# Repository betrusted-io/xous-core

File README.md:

# Xous Core

Xous is a microkernel operating system written in pure Rust, built for high-assurance applications.

Key features:
- Hardware memory protection
  - Virtual memory via MMU
  - Each process has an isolated address space
- `std` support in stable Rust (tier-3 Rust target)
- Asynchronous message passing
- Minimal code base
  - [Microkernel](./kernel) architecture
  - System [services](./services) live in userland
- Targeted at high-assurance embedded applications

The [Xous Book](https://betrusted.io/xous-book/) covers the architecture and structure of the kernel.

The [wiki](https://github.com/betrusted-io/betrusted-wiki/wiki) is a community resource that answers many FAQ.

The [Baochip README](./README-baochip.md) is the starting point for Baochip users. `vscode` users may wish to install the `baochip` extension to help manage build & test cycles.

USB CCID (smart-card class) on Baochip is documented in [`docs/ccid/`](./docs/ccid/). It is **not** enabled on default `dabao` / `baosec` images.

The [Precursor README](./README-precursor.md) is the starting point for Precursor users.

> [!IMPORTANT]
> Xous checks version tags as part of the build process. If building from a "shallow clone" or fork, fetch the tags, or else image creation will fail:
```
git remote add upstream https://github.com/betrusted-io/xous-core.git
git fetch upstream --tags
```

## Organization

Xous is a mono-repo project. It contains the kernel, libraries, applications, and tools necessary to build full device images. Here is a brief description of the more important directories:

* **api**: "Secular" API libraries - minimal-dependency, common-core APIs used by core Xous services
* **apps**: Precursor applications
* **apps-dabao**: Dabao applications
* **apps-baosec**: Baosec applications
* **bao1x-boot**: Bao1x secure boot chain
* **baremetal**: Baremetal target - runs after the boot chain, for developers that don't want Xous but can still use Xous' `no-std` features
* **emulation**: Renode scripts used to emulate Xous
* **imports**: Vendored-in libraries that had to be forked for Xous compatibility
* **kernel**: core memory manager, irq manager, and syscall implementations.
* **libs**: Device driver libraries. The common thread is that none of these code bases contain a `main.rs`, just a `lib.rs`.
* **loader**: Sets up virtual memory space and boots the kernel
* **locales**: Tools for handling internationalization
* **signing**: Scripts for generating signed images
* **services**: Xous programs that support Xous apps. Middleware, if you will.
* **svd2utra**: A program for converting SVD chip descriptions in XML to the UTRA "header file" format
* **tools**: Programs used to construct a final boot image. Also the home of various diagnostic and test utilities.
* **utralib**: The [Unambigous Thin Register Abtraction](./utralib/README.md). The core hardware interface for Xous.
* **xous-ipc**: Inter-process communication convenience APIs for Xous
* **xous-rs**: API files for the kernel. Where the syscall interfaces live.
* **xtask**: The build system manager for Xous.

## Dependencies

Install the latest [Rust](https://rust-lang.org/tools/install/) or run `rustup update` to update your Rust installation prior to building. Xous development assumes a recent version of Rust.

## Build Commands

- Precursor: `cargo xtask app-image`
- Dabao: `cargo xtask dabao`
- Dabao with USB CCID: `cargo xtask dabao-ccid`
- Baosec: `cargo xtask baosec`
- Baosec with USB CCID: `cargo xtask baosec-ccid`
- CCID HIL (echo personality, lab only): `cargo xtask ccid-hil`
- Baochip baremetal: `cargo xtask baremetal-bao1x`
- Defcon34: `cargo xtask baosec-lite dc34-console~flash dc34-vault`

Additional apps to be bundled into images can be specified as extra arguments on the command line, e.g. `cargo xtask dabao dabao-console` will generate a Dabao image that includes `dabao-console` in the detached-app section. Features, app-features, loader-features, and so forth can also be passed as command line arguments; run `cargo xtask` on its own for more help.

## Emulation

- `cargo xtask run` will bring up an emulated Precursor
- `cargo xtask baosec-emu` will bring up an emulated Baosec
- `cargo xtask renode-image` will build an image suitable for [Renode](https://renode.io/#downloads) emulation of a Precursor target. Start renode by running `renode emulation/xous-release.resc`

## Building Documentation
A flag of `--feature doc-deps` must be passed when running `cargo doc`, like this:

`cargo doc --no-deps --feature doc-deps`

`doc-deps` is a dummy hardware target that satisfies the requirement of
a "board" when building documentation.

## Local-vs-crates.io Verification

`xtask` does a check every build to ensure that any `crates.io` dependencies
are synchronized with the contents of the monorepo. It protects against the
scenario where you edited a crate that exists in the Xous repo, but the
build system ignores the local edits because it's fetching an old version from
`crates.io`.

Developers working on published crates should patch them in the root `Cargo.toml`
file and bypass the check with `--no-verify`.

## Acknowledgement
This project is funded through the NGI0 PET Fund, a fund established by NLnet
with financial support from the European Commission's Next Generation Internet
programme, under the aegis of DG Communications Networks, Content and Technology
under grant agreement No 825310.

<table>
    <tr>
        <td align="center" width="50%"></td>
        <td align="center"></td>
    </tr>
</table>

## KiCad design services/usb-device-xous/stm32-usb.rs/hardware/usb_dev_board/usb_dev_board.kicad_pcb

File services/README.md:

# Xous Services

Xous is a microkernel OS. The kernel itself is a small program, which runs within just one 4kiB page of RAM. The kernel in and of itself hands out pages from the page table, and routes messages. Everything else is managed by "servers".

Interprocess messages are fast and light-weight in Xous. `Scalar` messages pass data using registers on the stack, and are the fastest messages. `Memory` messages work by remapping memory pages between processes. `send`, `lend`, and `lend_mut` of memory pages is supported. `send` creates a full copy of the page, and is non-blocking; `lend` remaps the page into the borrowing process with read-only privileges, blocking the lending process until the borrowing process returns the page. `lend_mut` is like `lend` but with read/write privileges allowed on the lent memory.

The underlaying hardware is entirely memory-mapped; this includes the notional "disk" which is actually FLASH ROM. Every hardware peripheral has its addresses page-aligned, so that individual peripherals may be "owned" by a given server. The kernel itself "owns" no hardware other than a UART for debugging and a private port into the TRNG.

The kernel starts up a core set of servers, which are broadly divided into three categories:

- "Well known" servers
- "HAL" servers
- "Application" servers

Almost all servers in xous are accessed through a 128-bit, cryptographically random `SID`. These random IDs change with every boot. Thus, in order to connect to a server, one must first resolve its name into an `SID`. In order to facilitate this process, three "well known" servers are provided:

- `xous-names`
- `ticktimer-server`
- `log-server`

These three servers can be accessed by any process, regardless of their trust level, as their `SID` is actually a well-known number. The `ticktimer-server` is well-known so that servers can delay their boot (if necessary; so far it hasn't been). The `log-server` is well-known so that errors in connecting to the name server can be debugged.Please refer to the [README for xous-names](xous-names/README.md) for more details on how name resolution works.

Initially, `xous-names` functions as a permissive oracle that allows kernel servers to freely look up `SID`s using the set of names defined in [names.rs](../xous-rs/src/names.rs). Once the kernel is initialized, a `lockdown` message is sent to `xous-names` which prevents any further lookups on servers that are meant to be private to the kernel. (*TODO*: a coherent, maintainable method for declaring private servers to `xous-names`)

The distinction between "HAL" servers and "Application" servers is fuzzy; but as a rule of thumb, "HAL" servers are private to the kernel and strive for minimal complexity and maximal clarity in their writing. "Application" servers remain discoverable by user applications after the `lockdown` event, and are responsible for gate-keeping and vetting requests to the HAL layer.

An example of this is the `graphics-server` and the `gam`.

The `graphics-server` is a HAL; any process that can talk to it is capable of drawing pixels on the screen at any location. The `graphics-server` implements drawing primitives like `Rectangle`, `Line`, `Circle`, and `TextView`, as message-passing at the pixel level would not be performant. User processes should not be allowed to talk to it, because it would allow user processes to create a fake UI and thus could fool users into typing passwords into fake dialog boxes.

The `gam` is a Graphical Abstraction Manager. It manages various `Canvas` objects that have trust levels associated with them. Primitives such as `TextView` are bound to `Canvas` objects, and the `gam` will handle vetting if the objects are allowed to be drawn, clipping, and so forth. Note that the Xous philosophy is that applications do _not_ get to control the exact look-and-feel of their UI; this is to prevent less trusted applications from masquerading as trusted applications, but also assists with things like accessibility and internationalization. For example, applications cannot pick their font; they can only request a style class such as "small", "regular", and "bold". Thus application developers should think of rendering their UI more as hints and directives to the `gam`, and less as direct pixel pushing.

Conceptually, a complete Xous OS implementation would have HALs that claim the pages of every hardware device, and application servers that claim all the other remaining memory pages -- this includes unused pages and aliased regions -- except for the free memory reserved for applications themselves. Thus, Xous as a kernel does nothing to prevent anyone on its own right from mapping a page; it's up to the complete set of services frameworks to ensure that all the requisite pages have been mapped. (*TODO*: an audit tool to check the memory space and verify that 1. all CSRs and memory spaces explicitly declared in soc.svd are mapped, and 2. checks that otherwise remaining free space is mapped to a "gutter" that panics if accessed).

We're trying to track progress on implementing the various servers using [github projects](https://github.com/betrusted-io/xous-core/projects/1).

## Server Limit

Xous is currently limited to 128 servers. Each potential server reserves 40 bytes of space in the kernel. Xous 0.8 carries about 30 servers, so 128 servers should be reasonably future-proof. Adjusting the limit requires making a change in two places (note the permalink is to an older version of Xous):

1. https://github.com/betrusted-io/xous-core/blob/68aff967e85847cce98e6ec65384f59c803f18a8/kernel/src/services.rs#L19
1. https://github.com/betrusted-io/xous-core/blob/68aff967e85847cce98e6ec65384f59c803f18a8/kernel/src/services.rs#L235

Process count is adjusted by altering https://github.com/betrusted-io/xous-core/blob/master/kernel/src/arch/riscv/process.rs#L15. Xous 0.8 carries about 10 processes, and the current limit is 63. Each additional process reserves about 16 or so additional bytes for tracking information.

## Well-Known Servers
Here is the list of well-known services:
- `ticktimer-server` -- allows processes to know elapsed time since start, and request sleeps. Also manages WDT.
- `xous-names` -- resolves names into `SID`s.
- `log-server` -- implements info and error logging. Has a separate UART from the kernel UART.

## Hal Servers
Here are a list of HALs, implemented and projected, and their functions:

- `com` -- manages requests to and from the EC
- `graphics-server` -- manages the frame buffer and basic drawing primitives. Talks to the MEMLCD
- `keyboard` -- key matrix management; debounce; ScanCode conversion. Keyboard layouts (qwerty, dvorak, azerty, qwertz, braille) are interpreted in this server
- `trng` -- manages the TRNG hardware, provides TRNGs for other processes
- `llio` -- manages I2C, RTC, GPIO, pin interrupts, soft reboot, and power pins. Also home for info, build IDs, etc.
- `codec` -- basic buffering of frames into and out of the audio CODEC
- `jtag` -- manages the JTAG interface (used for key fusing)
- `keys` -- management of cryptographic key store
- `engine25519` -- Engine25519 interface
- `sha512` -- SHA512 interface
- `spinor` -- manages the erasure and programming of the SPINOR
- `ram` -- manages allocation of RAM for applications
- `scheduler` -- manages thread scheduling and priorities

## Application Servers
Here are a list of application servers, implemented and projected, and their functions:
- `fcc-agent` -- use-once -- a special agent meant to run on a minimal Xous for FCC testing. Should never be compiled into production firmware.
- `trng-tester` -- use-once -- a special server used to facilitate testing of the TRNG. Pipes TRNG output to memory regions that can be read out using `bt-rngd` and fed into Dieharder for analysis.
- `gam` -- pre-alpha -- manages `Canvas` objects, and provides an abstract framework for applications. Also manages status bar, context menus and pop-up notifications.
- `ime` -- liases with `keyboard` and `gam` to handle keyboard input
- `pddb` -- plausibly deniable database. Used in lieu of a conventional filesystem for storing key/value pairs in a plausibly deniable fashion.
- `update-ec` -- manages the updating of the EC
- `update-soc` -- manages remote (non-USB) updates of the FPGA and kernel
- `net` -- manages connections to the Internet
- `wifi` -- manages wifi configuration
- `power` -- intermediates requests to the backlight, battery status, charging, RTC, etc.
- `accel` -- intermediates requests to the accelerometer
- `audio` -- intermediates requests to the audio hardware. Does stream mixing, etc.
- `usb` -- handles USB connections
- `credentials` -- trusted PIN/password entry mechanism, manages currently activated credentials

## Applications
Here are a list of user applications:
- `shell` -- refactoring -- provides a "chat-like" interface for talking to Xous
- `chat` -- text and audio secure chat app
- `launcher` -- an application launcher
- `password` -- a password vault

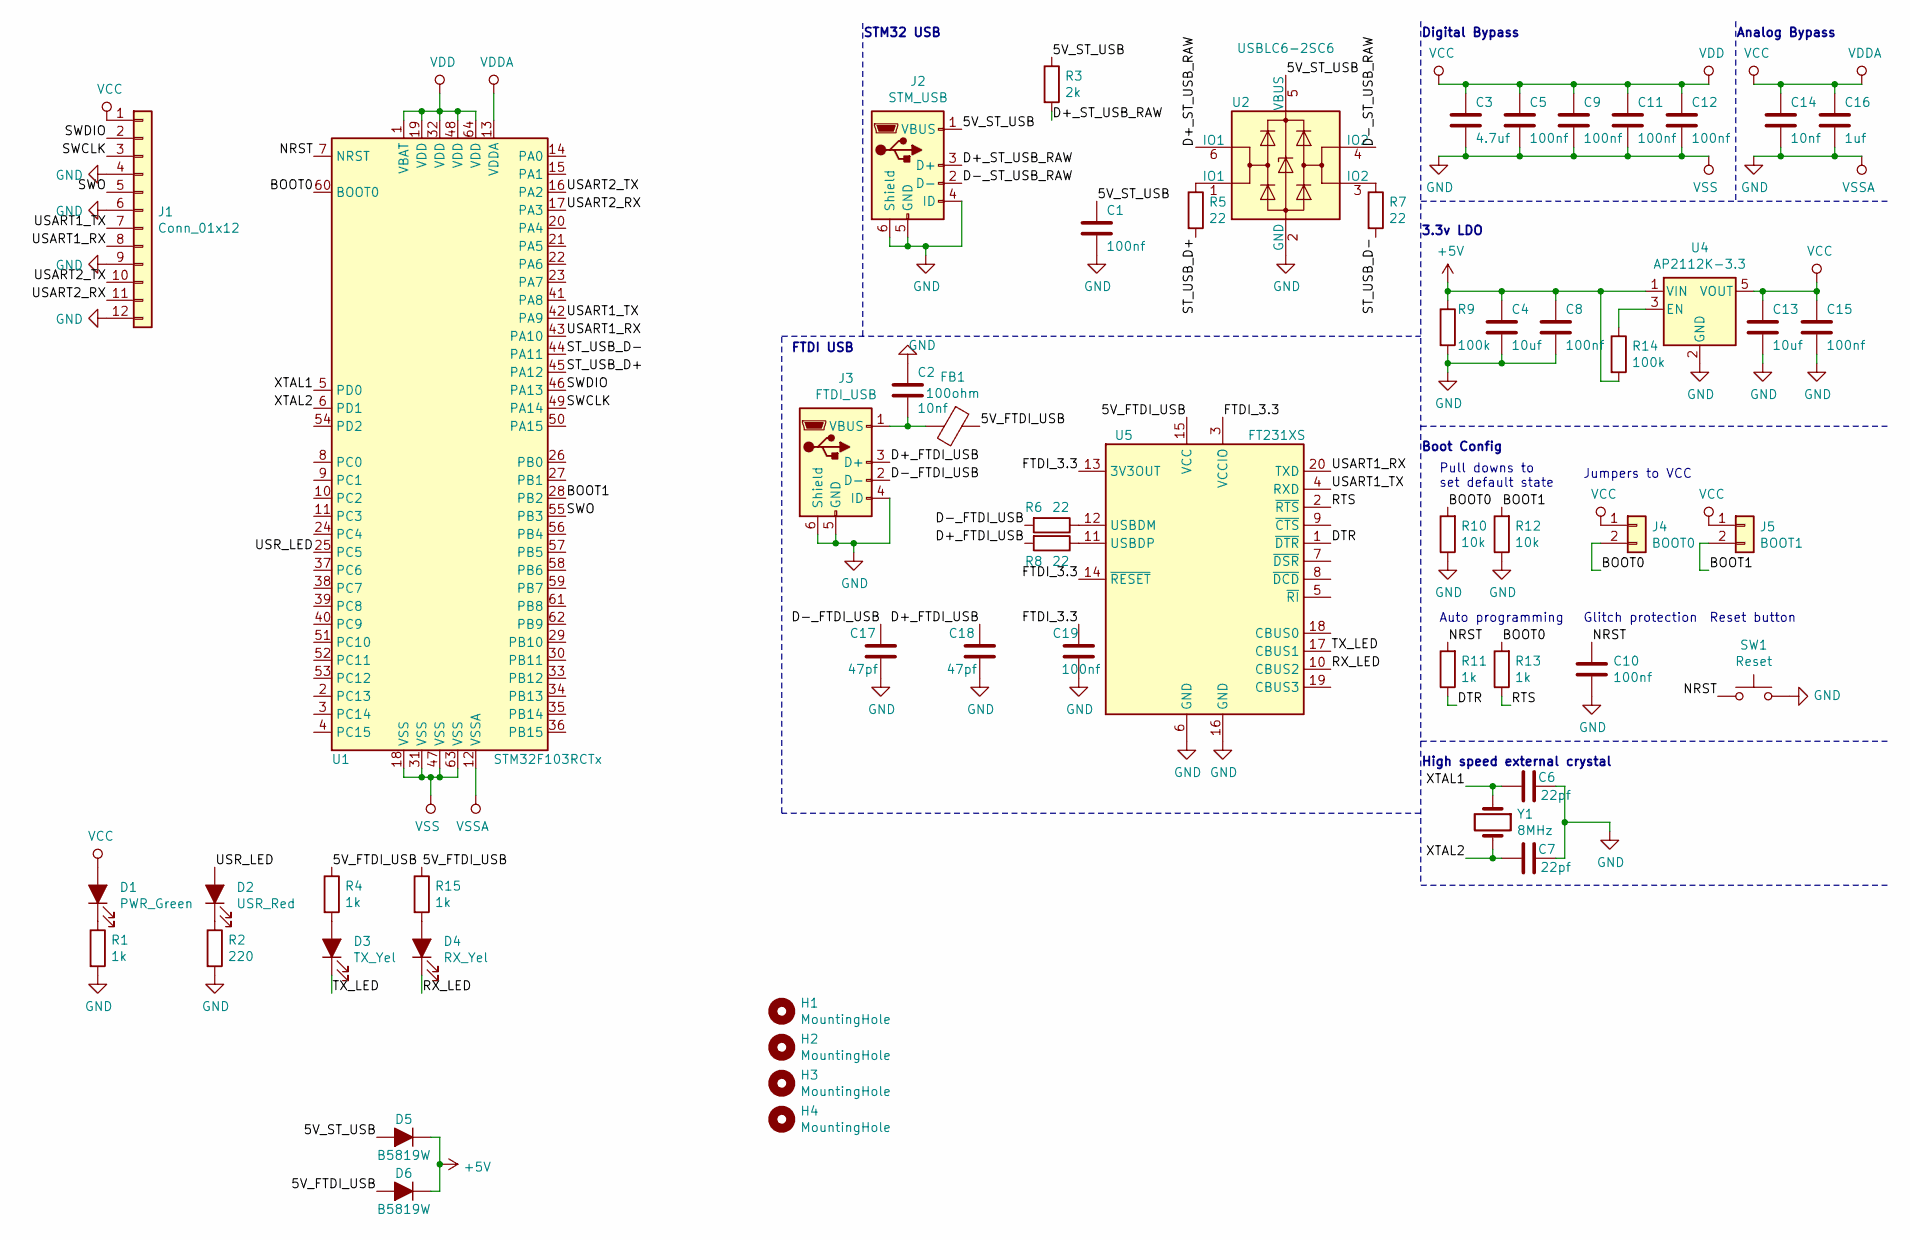
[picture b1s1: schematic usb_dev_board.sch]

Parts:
C1, C5, C8, C9, C10, C11, C12, C15, C19: 100nf; C_0402_1005Metric; Part Number CL05B104KO5NNNC; LCSC Part Number C1525
C2, C14: 10nf; C_0402_1005Metric; Part Number CL05B103KB5NNNC; LCSC Part Number C15195
C3: 4.7uf; C_0402_1005Metric; Part Number CL05A475MP5NRNC; LCSC Part Number C23733
C4, C13: 10uf; C_0402_1005Metric; Part Number CL05A106MQ5NUNC; LCSC Part Number C15525
C6, C7: 22pf; C_0402_1005Metric; Part Number 0402CG220J500NT; LCSC Part Number C1555
C16: 1uf; C_0402_1005Metric; Part Number CL05A105KA5NQNC; LCSC Part Number C52923
C17, C18: 47pf; C_0402_1005Metric; Part Number 0402CG470J500NT; LCSC Part Number C1567
D1: PWR_Green; LED_0603_1608Metric; Part Number 19-217/GHC-YR1S2/3T; LCSC Part Number C72043
D2: USR_Red; LED_0603_1608Metric; Part Number 红灯 0603; LCSC Part Number C2286
D3: TX_Yel; LED_0603_1608Metric; Part Number 19-213/Y2C-CQ2R2L/3T(CY); LCSC Part Number C72038
D4: RX_Yel; LED_0603_1608Metric; Part Number 19-213/Y2C-CQ2R2L/3T(CY); LCSC Part Number C72038
D5, D6: B5819W; D_SOD-123; Part Number B5819W; LCSC Part Number C8598
FB1: 100ohm; L_0805_2012Metric; Part Number GZ2012D101TF; LCSC Part Number C1015
H1, H2, H3, H4: MountingHole; MountingHole_4.3mm_M4
J1: Conn_01x12; PinHeader_1x12_P2.54mm_Vertical
J2: STM_USB; USB_MICRO_B_U-F-M5DD-W-2; Part Number U-D-M7DS-G-2; LCSC Part Number C319154
J3: FTDI_USB; USB_MICRO_B_U-F-M5DD-W-2; Part Number U-D-M7DS-G-2; LCSC Part Number C319154
J4: BOOT0; PinHeader_1x02_P2.54mm_Vertical
J5: BOOT1; PinHeader_1x02_P2.54mm_Vertical
R1, R4, R11, R13, R15: 1k; R_0402_1005Metric; Part Number 0402WGF1001TCE; LCSC Part Number C11702
R2: 220; R_0402_1005Metric; Part Number 0402WGF2200TCE; LCSC Part Number C25091
R3: 2k; R_0402_1005Metric; Part Number 0402WGF2001TCE; LCSC Part Number C4109
R5, R6, R7, R8: 22; R_0402_1005Metric; Part Number 0402WGF220JTCE; LCSC Part Number C25092
R9, R14: 100k; R_0402_1005Metric; Part Number 0402WGF1003TCE; LCSC Part Number C25741
R10, R12: 10k; R_0402_1005Metric; Part Number 0402WGF1002TCE; LCSC Part Number C25744
SW1: Reset; SW_SPST_B3SL-1002P; Part Number TS-1187A-B-A-B; LCSC Part Number C318884
U1: STM32F103RCTx; LQFP-64_10x10mm_P0.5mm; Part Number STM32F103RCT6; LCSC Part Number C8323
U2: USBLC6-2SC6; SOT-23-6; Part Number USBLC6-2SC6; LCSC Part Number C7519
U4: AP2112K-3.3; SOT-23-5; Part Number AP2112K-3.3TRG1; LCSC Part Number C51118
U5: FT231XS; SSOP-20_3.9x8.7mm_P0.635mm; Part Number FT231XS-U; LCSC Part Number C89607
Y1: 8MHz; Crystal_SMD_5032-2Pin_5.0x3.2mm; Part Number X50328MSB2GI; LCSC Part Number C115962

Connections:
+5V: C4.1, C8.1, D5.1 (K), D6.1 (K), R9.1, R14.2, U4.1 (VIN)
/5V_FTDI_USB: D6.2 (A), FB1.1, R4.1, R15.1, U5.15 (VCC)
/5V_ST_USB: C1.1, D5.2 (A), J2.1 (VBUS), R3.1, U2.5 (VBUS)
/BOOT0: J4.2, R10.2, R13.2, U1.60 (BOOT0)
/BOOT1: J5.2, R12.2, U1.28 (PB2)
/D+_FTDI_USB: C18.1, J3.3 (D+), R8.2
/D+_ST_USB_RAW: J2.3 (D+), R3.2, U2.6 (IO1)
/D-_FTDI_USB: C17.1, J3.2 (D-), R6.2
/D-_ST_USB_RAW: J2.2 (D-), U2.4 (IO2)
/DTR: R11.1, U5.1 (~DTR)
/FTDI_3.3: C19.1, U5.3 (VCCIO), U5.13 (3V3OUT), U5.14 (~RESET)
/NRST: C10.1, R11.2, SW1.1, U1.7 (NRST)
/RTS: R13.1, U5.2 (~RTS)
/RX_LED: D4.1 (K), U5.10 (CBUS2)
/ST_USB_D+: R5.2, U1.45 (PA12)
/ST_USB_D-: R7.2, U1.44 (PA11)
/SWCLK: J1.3, U1.49 (PA14)
/SWDIO: J1.2, U1.46 (PA13)
/SWO: J1.5, U1.55 (PB3)
/TX_LED: D3.1 (K), U5.17 (CBUS1)
/USART1_RX: J1.8, U1.43 (PA10), U5.20 (TXD)
/USART1_TX: J1.7, U1.42 (PA9), U5.4 (RXD)
/USART2_RX: J1.11, U1.17 (PA3)
/USART2_TX: J1.10, U1.16 (PA2)
/USR_LED: D2.2 (A), U1.25 (PC5)
/XTAL1: C6.2, U1.5 (PD0), Y1.1
/XTAL2: C7.2, U1.6 (PD1), Y1.2
GND: C1.2, C2.1, C3.2, C4.2, C5.2, C6.1, C7.1, C8.2, C9.2, C10.2, C11.2, C12.2, C13.2, C14.2, C15.2, C16.2, C17.2, C18.2, C19.2, J1.4, J1.6, J1.9, J1.12, J2.4 (ID), J2.5 (GND), J2.6 (Shield), J3.4 (ID), J3.5 (GND), J3.6 (Shield), R1.2, R2.2, R9.2, R10.1, R12.1, SW1.2, U1.12 (VSSA), U1.18 (VSS), U1.31 (VSS), U1.47 (VSS), U1.63 (VSS), U2.2 (GND), U4.2 (GND), U5.6 (GND), U5.16 (GND)
unnamed: C2.2, FB1.2, J3.1 (VBUS)
unnamed: D1.1 (K), R1.1
unnamed: D2.1 (K), R2.1
unnamed: D3.2 (A), R4.2
unnamed: D4.2 (A), R15.2
unnamed: R5.1, U2.1 (IO1)
unnamed: R6.1, U5.12 (USBDM)
unnamed: R7.1, U2.3 (IO2)
unnamed: R8.1, U5.11 (USBDP)
unnamed: R14.1, U4.3 (EN)
VCC: C3.1, C5.1, C9.1, C11.1, C12.1, C13.1, C14.1, C15.1, C16.1, D1.2 (A), J1.1, J4.1, J5.1, U1.1 (VBAT), U1.13 (VDDA), U1.19 (VDD), U1.32 (VDD), U1.48 (VDD), U1.64 (VDD), U4.5 (VOUT)

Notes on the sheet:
Analog Bypass
Digital Bypass
3.3v LDO
Boot Config
Pull downs to set default state
Jumpers to VCC
Auto programming
Glitch protection
High speed external crystal
Reset button
STM32 USB
FTDI USB

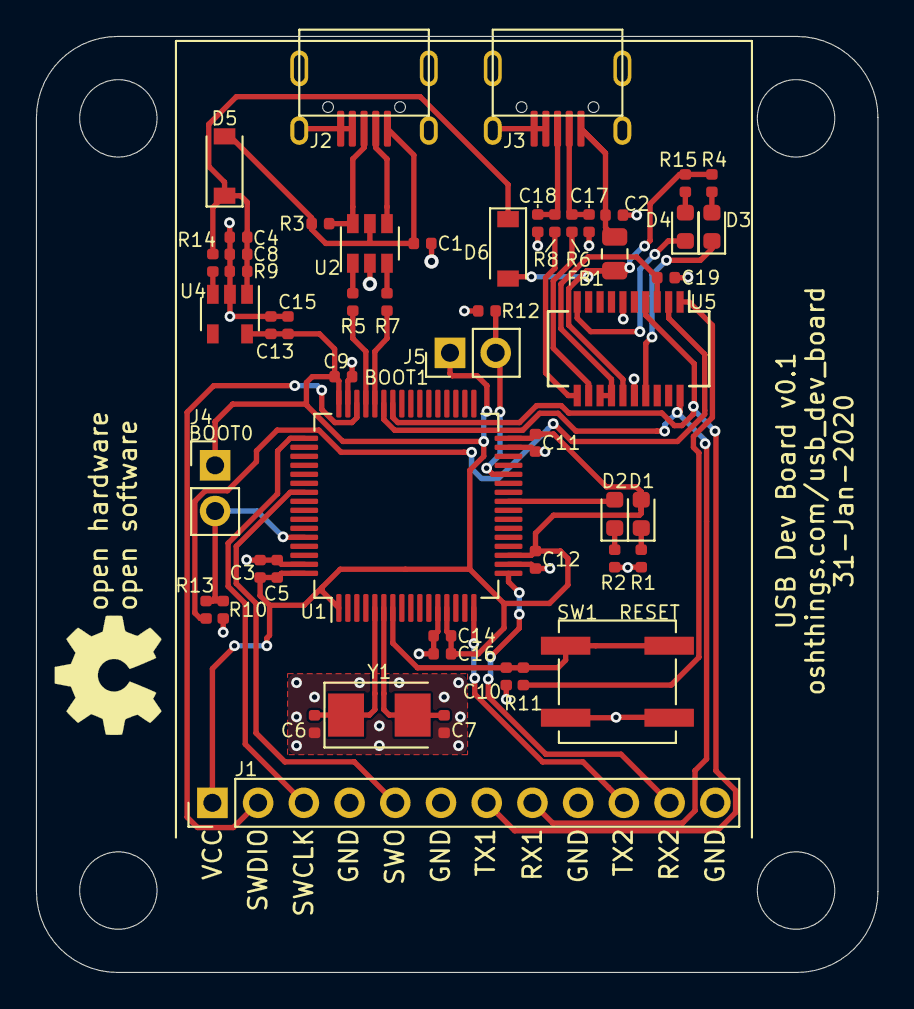
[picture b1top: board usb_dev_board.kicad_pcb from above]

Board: 2 copper layers, 46.8 x 52.0 mm, 56 parts (0 on the bottom side), 39 nets.
